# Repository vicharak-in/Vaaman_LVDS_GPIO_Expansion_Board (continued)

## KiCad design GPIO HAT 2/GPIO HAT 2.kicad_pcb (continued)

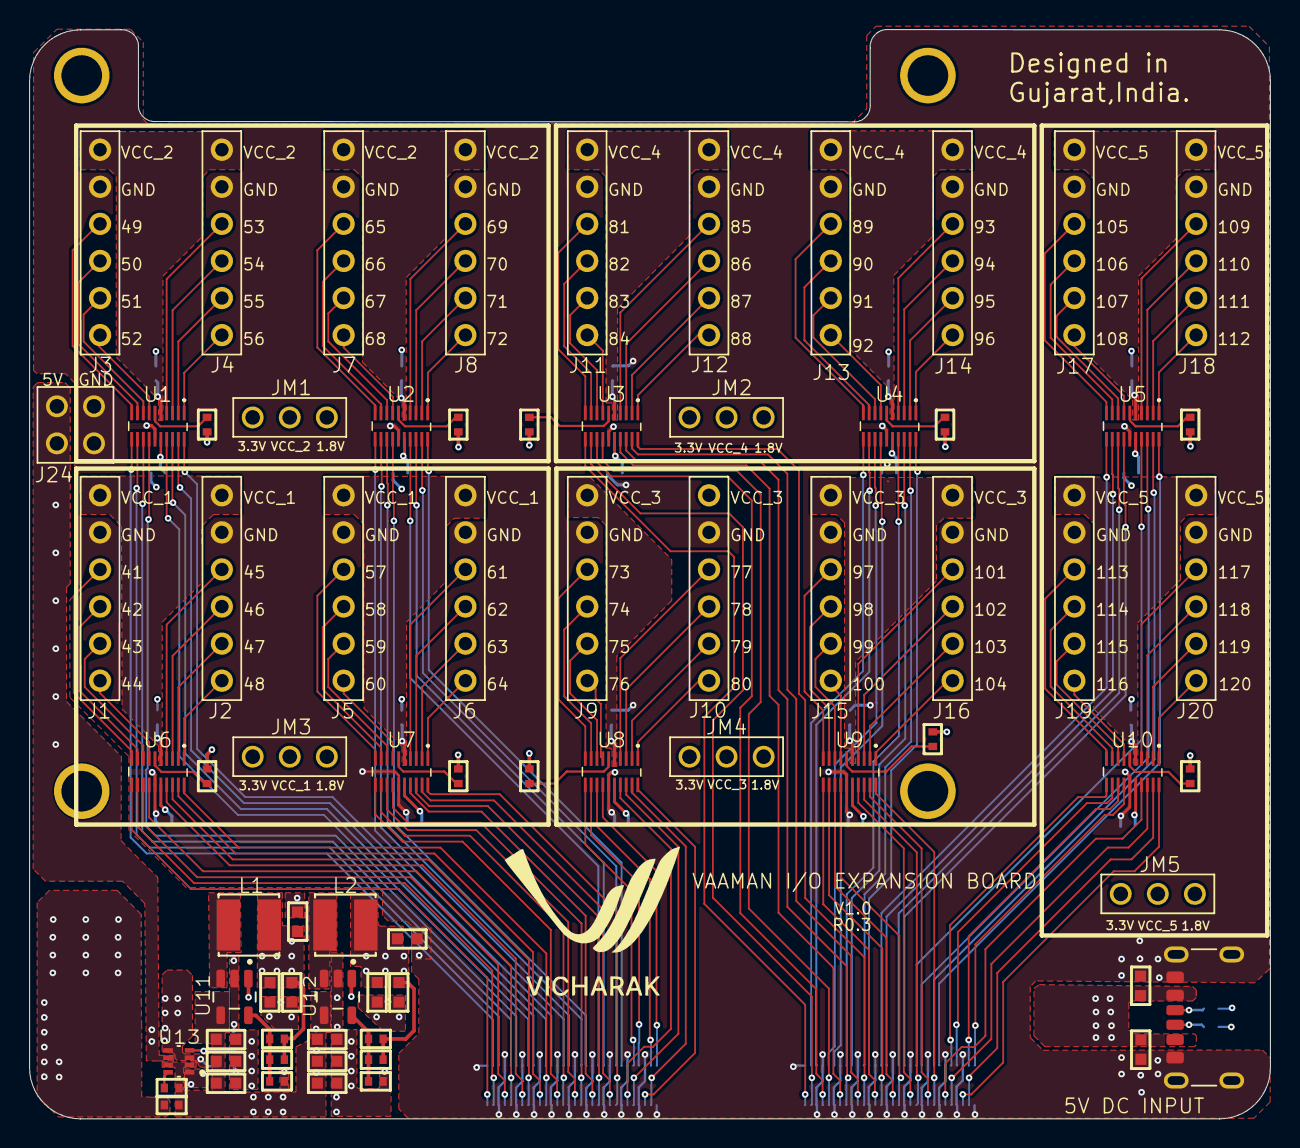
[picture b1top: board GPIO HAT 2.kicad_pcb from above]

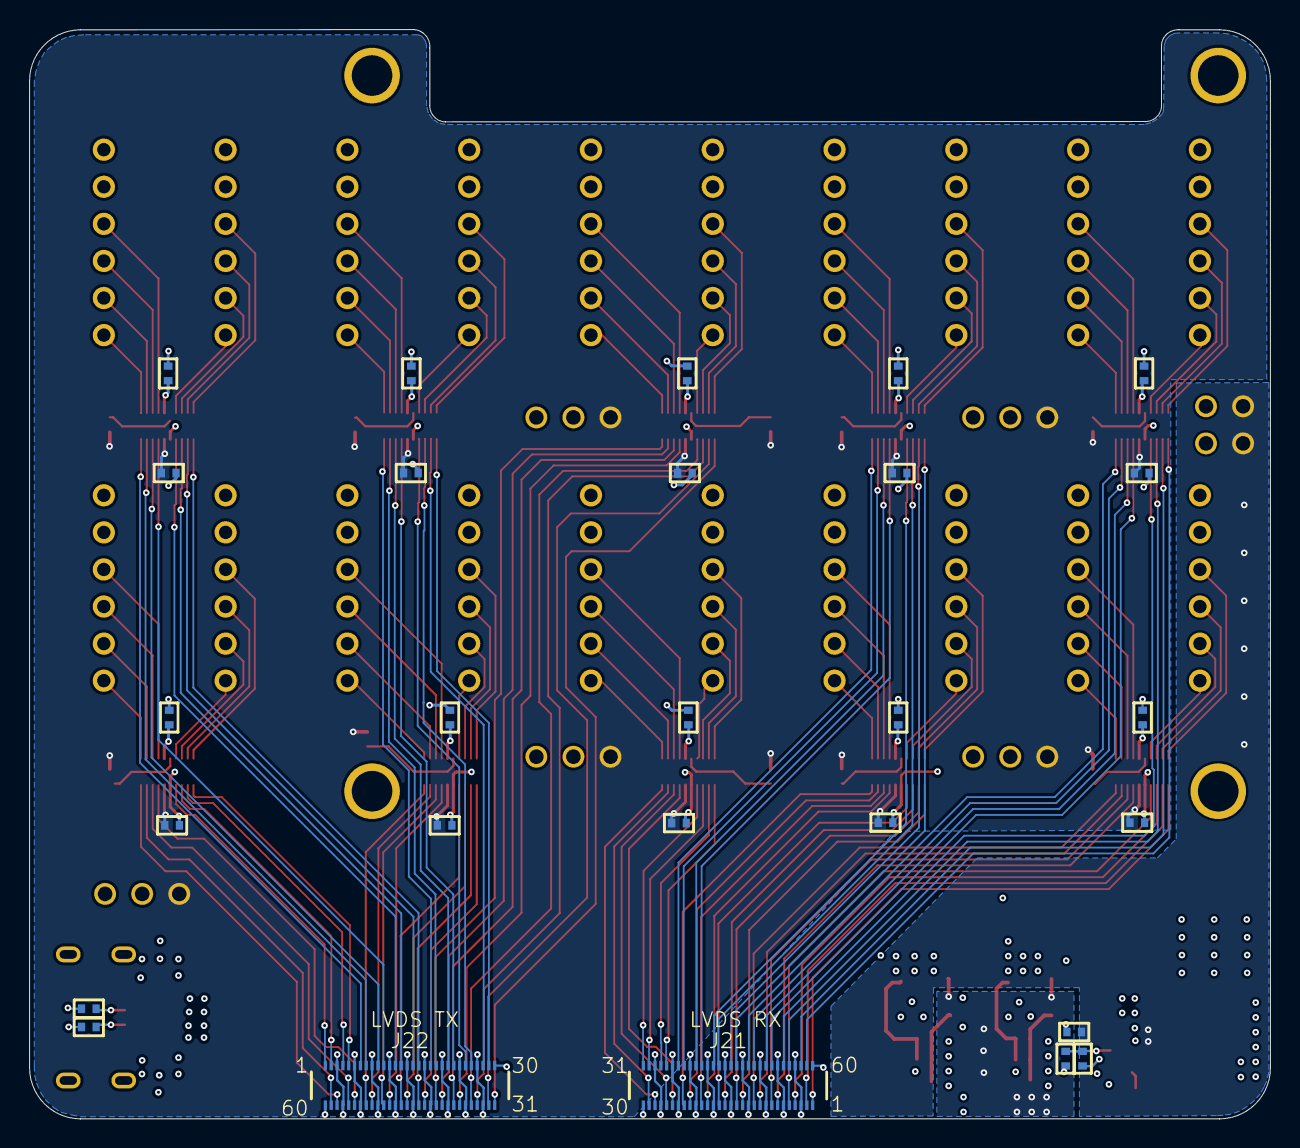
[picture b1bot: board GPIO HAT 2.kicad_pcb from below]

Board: 4 copper layers, 85.0 x 74.6 mm, 101 parts (27 on the bottom side), 189 nets.

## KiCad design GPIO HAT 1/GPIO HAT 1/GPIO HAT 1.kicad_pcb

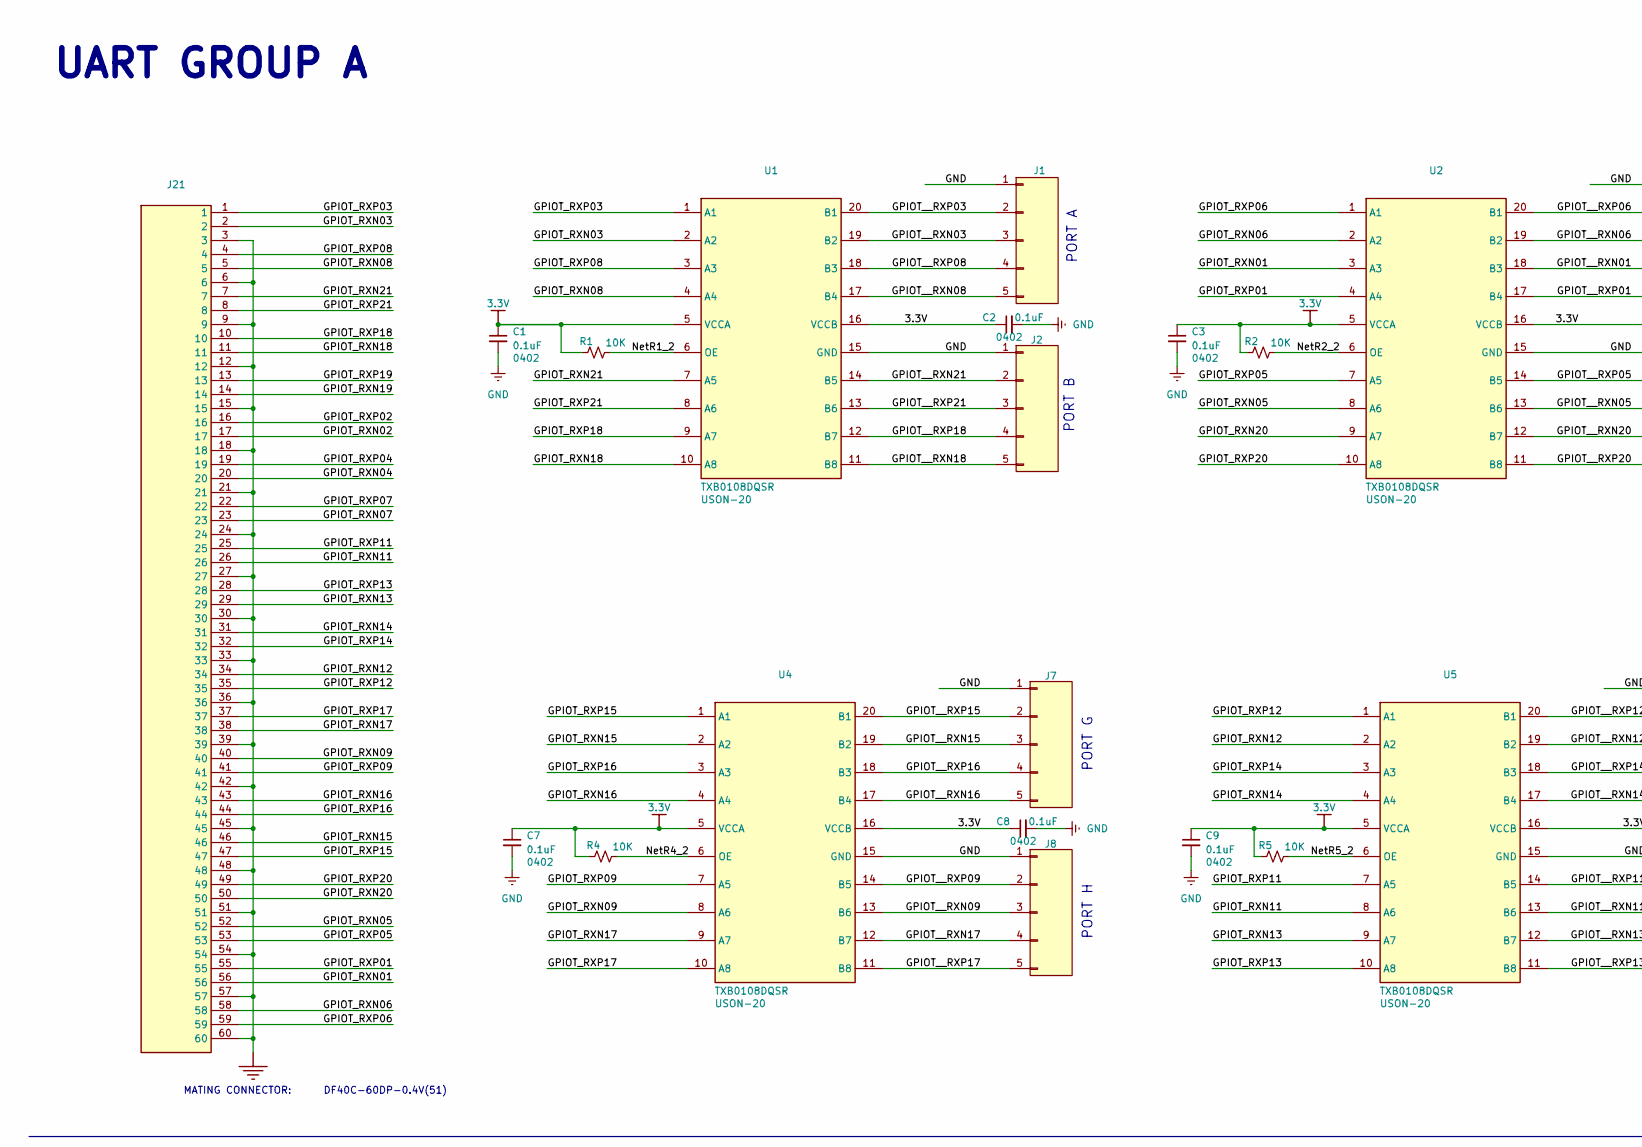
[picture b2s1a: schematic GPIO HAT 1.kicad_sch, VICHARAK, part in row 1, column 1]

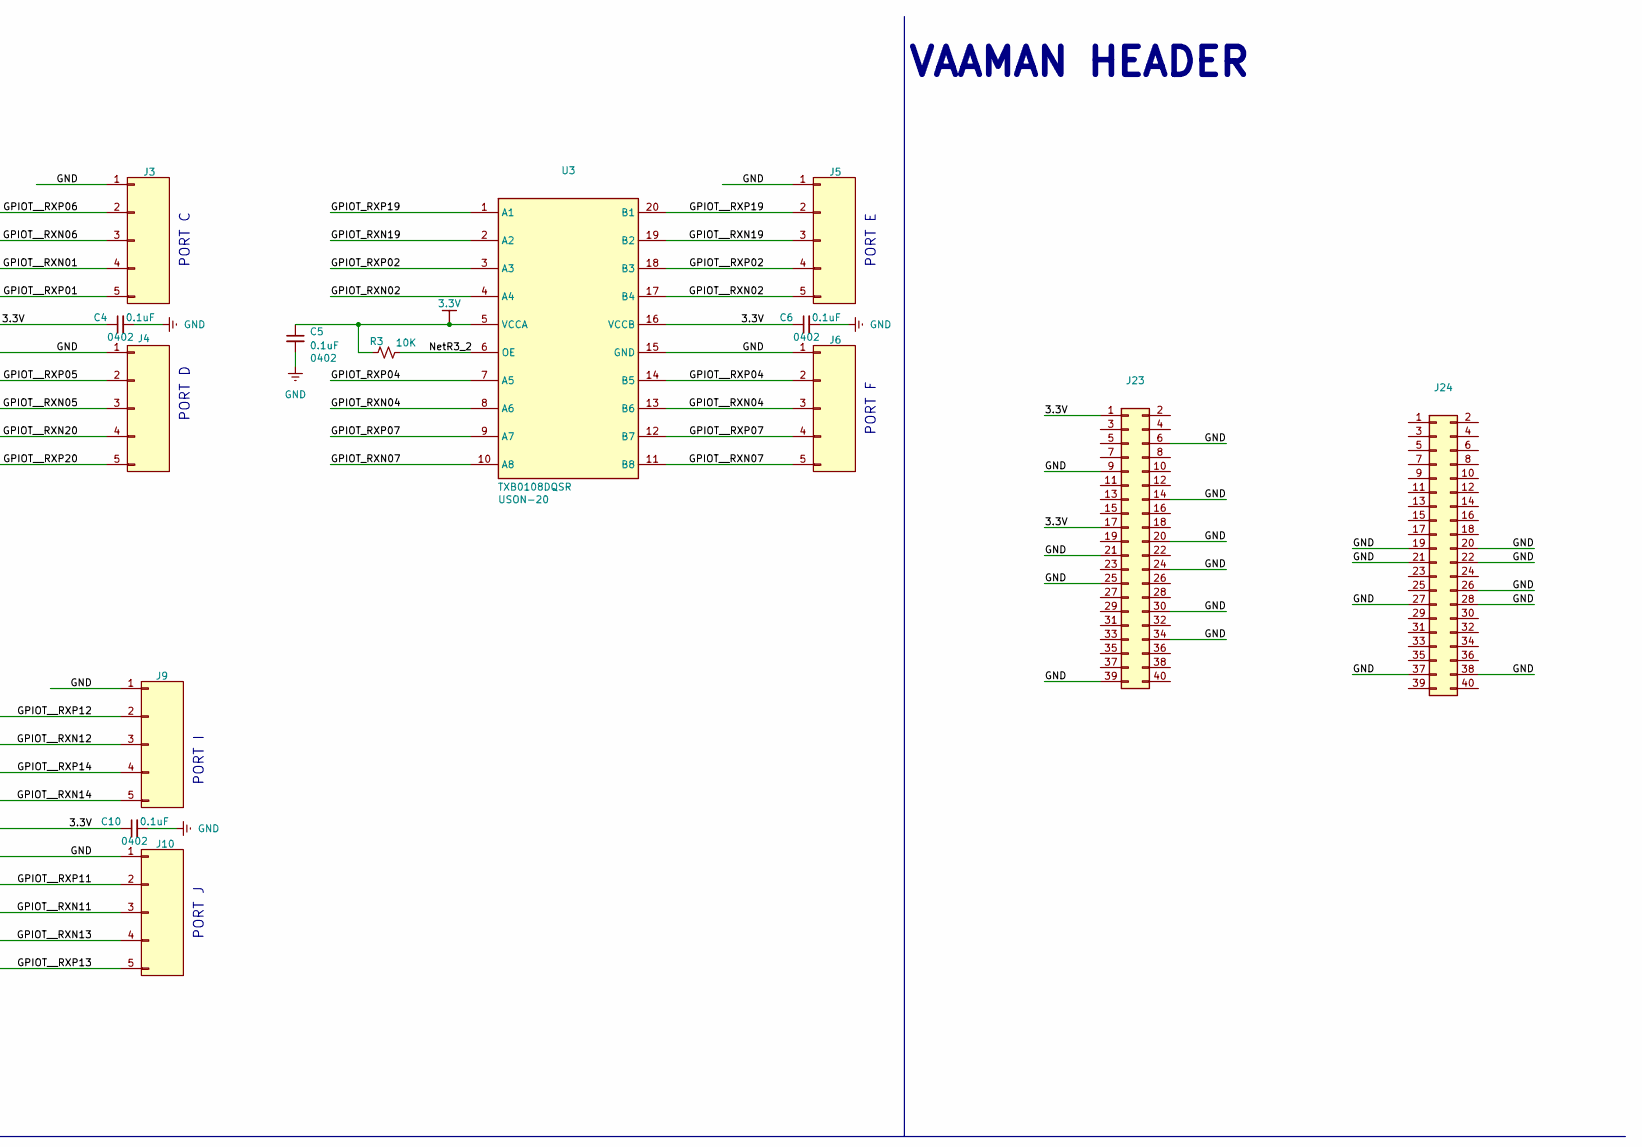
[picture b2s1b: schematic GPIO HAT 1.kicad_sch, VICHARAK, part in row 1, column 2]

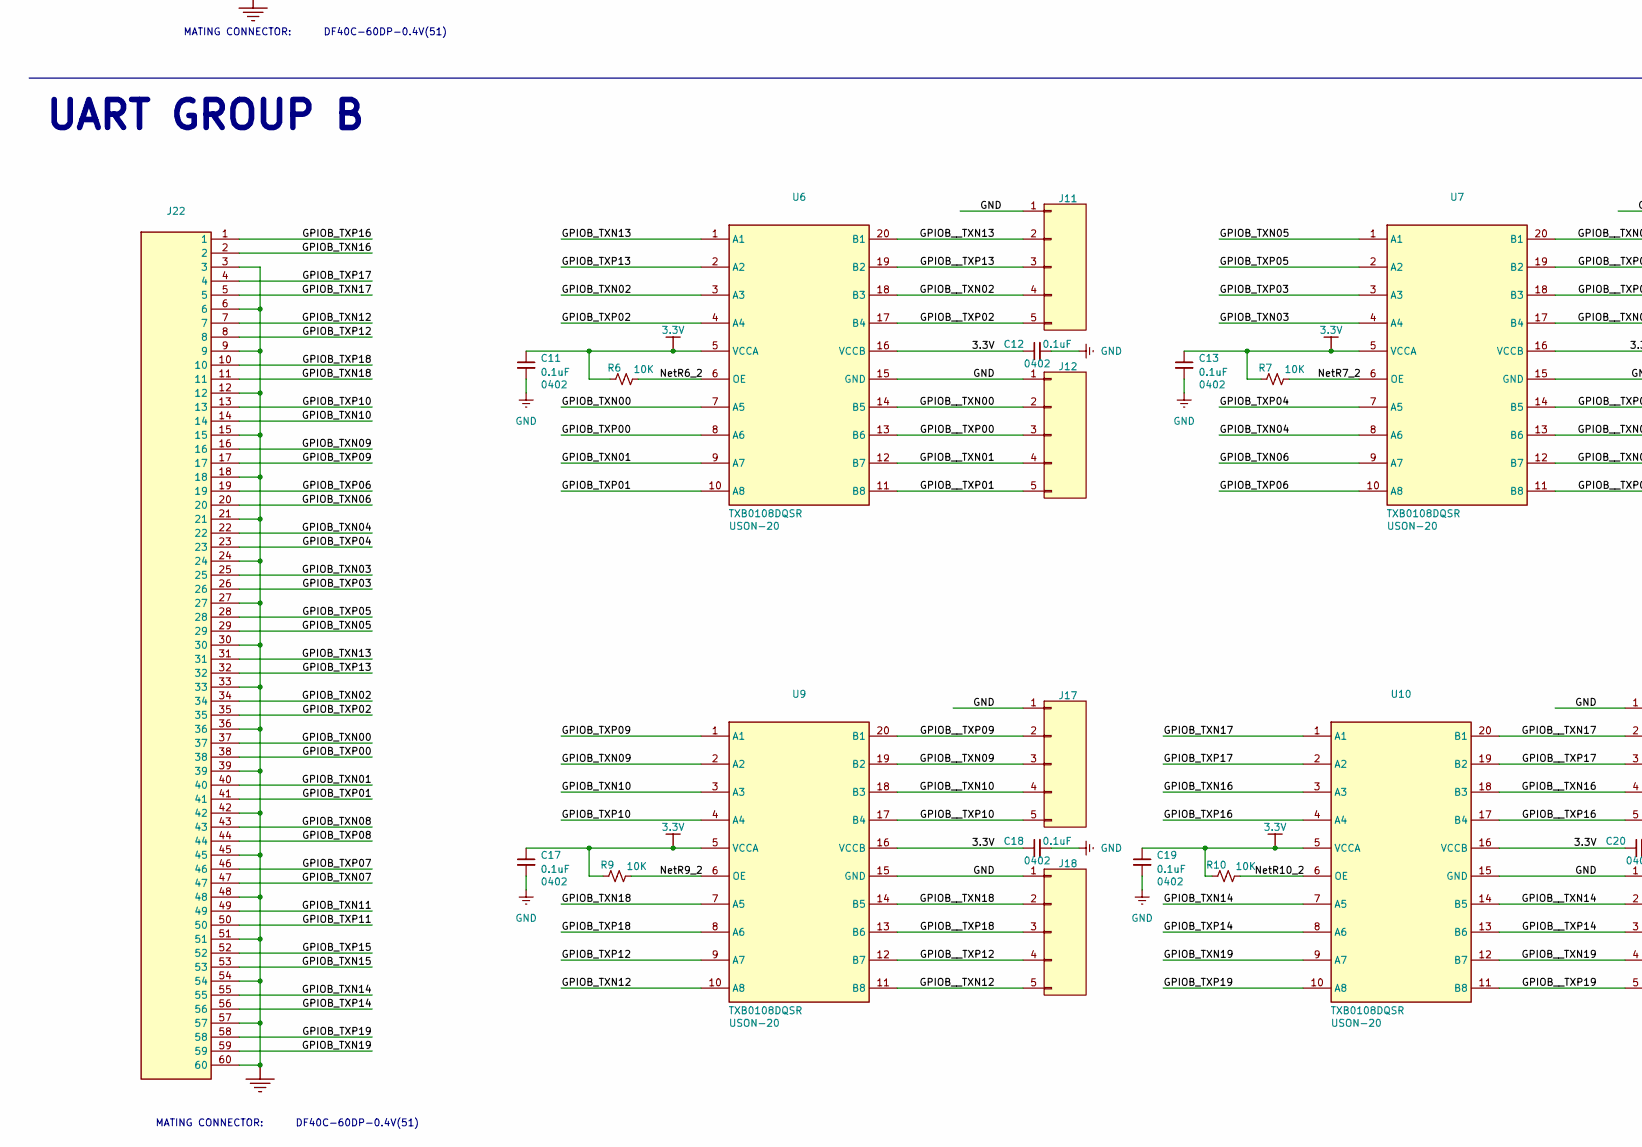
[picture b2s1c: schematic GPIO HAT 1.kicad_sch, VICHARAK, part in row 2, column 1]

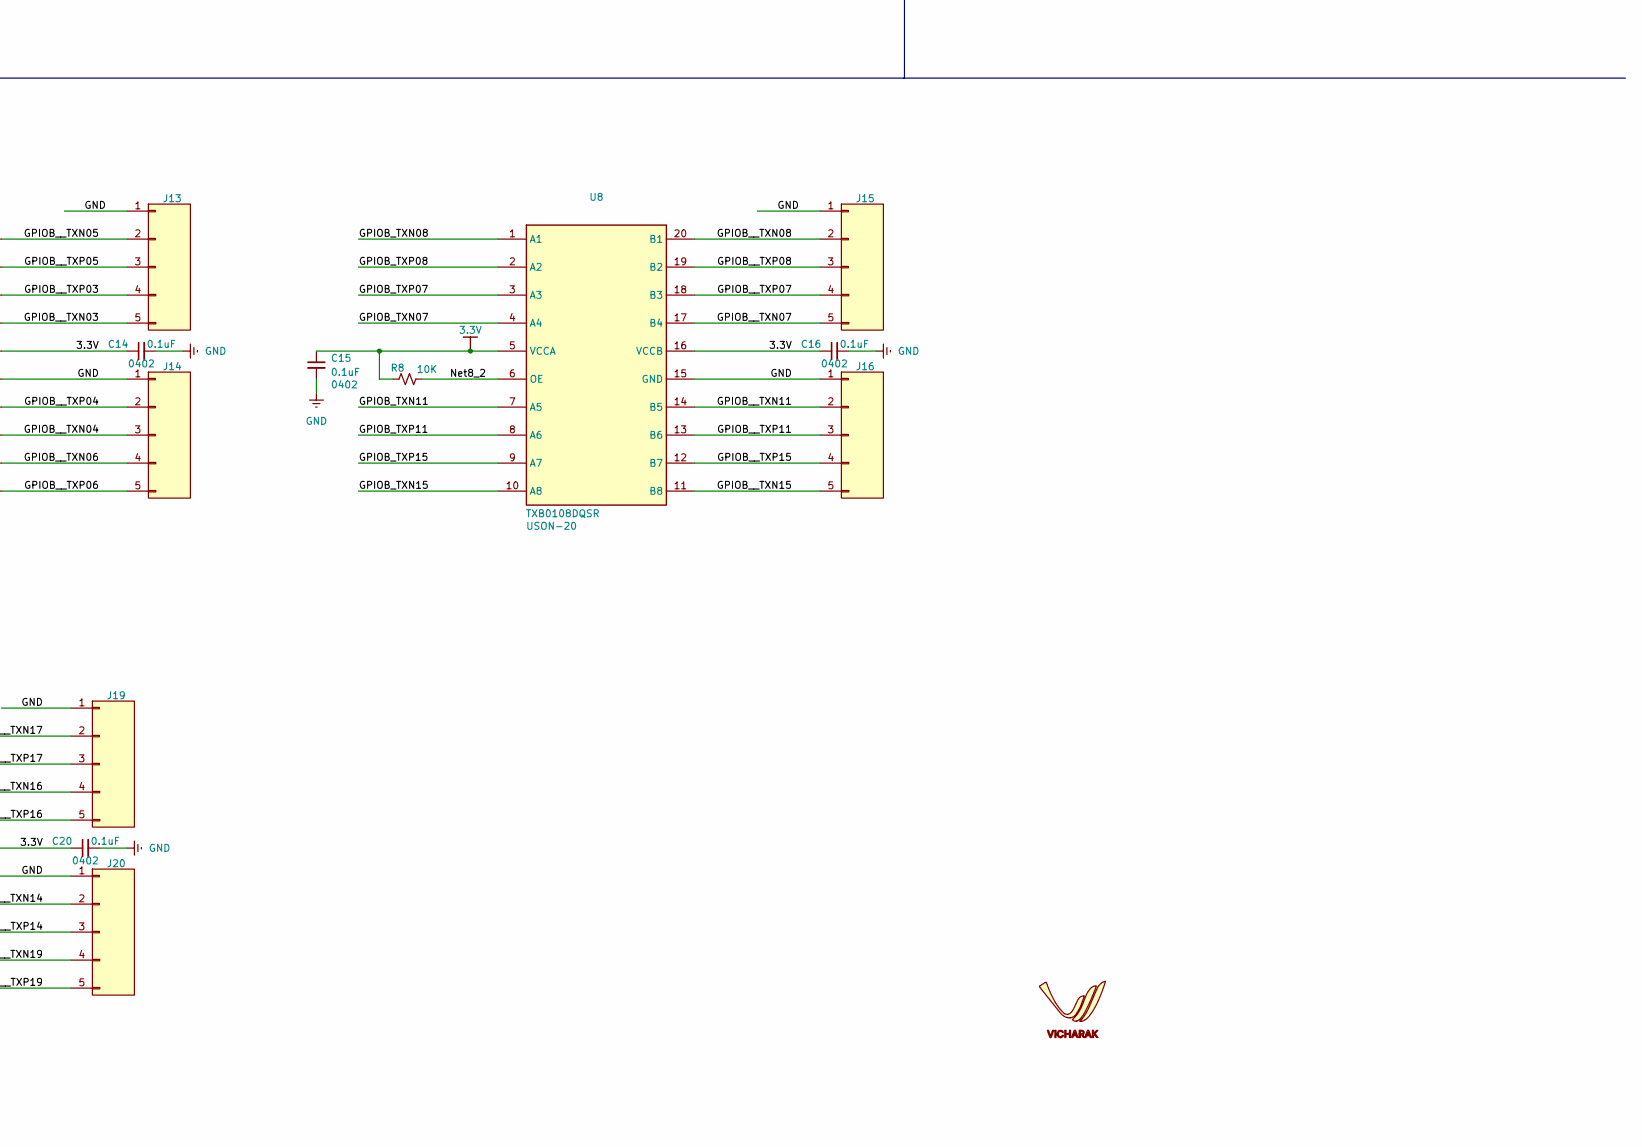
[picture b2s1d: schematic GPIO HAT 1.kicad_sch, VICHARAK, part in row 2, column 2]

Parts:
C1, C2, C3, C4, C5, C6, C7, C8, C9, C10, C11, C12, C13, C14, C15, C16, C17, C18, C19, C20: 0.1uF; CAP0402
J1, J2, J3, J4, J5, J6, J7, J8, J9, J10, J11, J12, J13, J14, J15, J16, J17, J18, J19, J20: Conn_01x05; 01x05 Header 2.54mm
J21, J22: LVDS2; Mouser Part Number 798-DF40C60DS0.4V51
J23, J24: 2.54-2*20PPC104; 2x20 header; MANUFACTURER PART NUMBER 2.54-2*20PPC104
R1, R2, R3, R4, R5, R6, R7, R8, R9, R10: 10K; RES0402_10K
U1, U2, U3, U4, U5, U6, U7, U8, U9, U10: TXB0108DQSR; Mouser Part Number 595-TXB0108DQSR

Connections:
3.3V: C1.1, C2.1, C3.1, C4.1, C5.1, C6.1, C7.1, C8.1, C9.1, C10.1, C11.1, C12.1, C13.1, C14.1, C15.1, C16.1, C17.1, C18.1, C19.1, C20.1, J23.1, J23.17, R1.1, R2.1, R3.1, R4.1, R5.1, R6.1, R7.1, R8.1, R9.1, R10.1, U1.5 (VCCA), U1.16 (VCCB), U2.5 (VCCA), U2.16 (VCCB), U3.5 (VCCA), U3.16 (VCCB), U4.5 (VCCA), U4.16 (VCCB), U5.5 (VCCA), U5.16 (VCCB), U6.5 (VCCA), U6.16 (VCCB), U7.5 (VCCA), U7.16 (VCCB), U8.5 (VCCA), U8.16 (VCCB), U9.5 (VCCA), U9.16 (VCCB), U10.5 (VCCA), U10.16 (VCCB)
/GPIOB_TXN00: J22.37, U6.7 (A5)
/GPIOB_TXN01: J22.40, U6.9 (A7)
/GPIOB_TXN02: J22.34, U6.3 (A3)
/GPIOB_TXN03: J22.25, U7.4 (A4)
/GPIOB_TXN04: J22.22, U7.8 (A6)
/GPIOB_TXN05: J22.29, U7.1 (A1)
/GPIOB_TXN06: J22.20, U7.9 (A7)
/GPIOB_TXN07: J22.47, U8.4 (A4)
/GPIOB_TXN08: J22.43, U8.1 (A1)
/GPIOB_TXN09: J22.16, U9.2 (A2)
/GPIOB_TXN10: J22.14, U9.3 (A3)
/GPIOB_TXN11: J22.49, U8.7 (A5)
/GPIOB_TXN12: J22.7, U9.10 (A8)
/GPIOB_TXN13: J22.31, U6.1 (A1)
/GPIOB_TXN14: J22.55, U10.7 (A5)
/GPIOB_TXN15: J22.53, U8.10 (A8)
/GPIOB_TXN16: J22.2, U10.3 (A3)
/GPIOB_TXN17: J22.5, U10.1 (A1)
/GPIOB_TXN18: J22.11, U9.7 (A5)
/GPIOB_TXN19: J22.59, U10.9 (A7)
/GPIOB_TXP00: J22.38, U6.8 (A6)
/GPIOB_TXP01: J22.41, U6.10 (A8)
/GPIOB_TXP02: J22.35, U6.4 (A4)
/GPIOB_TXP03: J22.26, U7.3 (A3)
/GPIOB_TXP04: J22.23, U7.7 (A5)
/GPIOB_TXP05: J22.28, U7.2 (A2)
/GPIOB_TXP06: J22.19, U7.10 (A8)
/GPIOB_TXP07: J22.46, U8.3 (A3)
/GPIOB_TXP08: J22.44, U8.2 (A2)
/GPIOB_TXP09: J22.17, U9.1 (A1)
/GPIOB_TXP10: J22.13, U9.4 (A4)
/GPIOB_TXP11: J22.50, U8.8 (A6)
/GPIOB_TXP12: J22.8, U9.9 (A7)
/GPIOB_TXP13: J22.32, U6.2 (A2)
/GPIOB_TXP14: J22.56, U10.8 (A6)
/GPIOB_TXP15: J22.52, U8.9 (A7)
/GPIOB_TXP16: J22.1, U10.4 (A4)
/GPIOB_TXP17: J22.4, U10.2 (A2)
/GPIOB_TXP18: J22.10, U9.8 (A6)
/GPIOB_TXP19: J22.58, U10.10 (A8)
/GPIOB__TXN00: J12.2, U6.14 (B5)
/GPIOB__TXN01: J12.4, U6.12 (B7)
/GPIOB__TXN02: J11.4, U6.18 (B3)
/GPIOB__TXN03: J13.5, U7.17 (B4)
/GPIOB__TXN04: J14.3, U7.13 (B6)
/GPIOB__TXN05: J13.2, U7.20 (B1)
/GPIOB__TXN06: J14.4, U7.12 (B7)
/GPIOB__TXN07: J15.5, U8.17 (B4)
/GPIOB__TXN08: J15.2, U8.20 (B1)
/GPIOB__TXN09: J17.3, U9.19 (B2)
/GPIOB__TXN10: J17.4, U9.18 (B3)
/GPIOB__TXN11: J16.2, U8.14 (B5)
/GPIOB__TXN12: J18.5, U9.11 (B8)
/GPIOB__TXN13: J11.2, U6.20 (B1)
/GPIOB__TXN14: J20.2, U10.14 (B5)
/GPIOB__TXN15: J16.5, U8.11 (B8)
/GPIOB__TXN16: J19.4, U10.18 (B3)
/GPIOB__TXN17: J19.2, U10.20 (B1)
/GPIOB__TXN18: J18.2, U9.14 (B5)
/GPIOB__TXN19: J20.4, U10.12 (B7)
/GPIOB__TXP00: J12.3, U6.13 (B6)
/GPIOB__TXP01: J12.5, U6.11 (B8)
/GPIOB__TXP02: J11.5, U6.17 (B4)
/GPIOB__TXP03: J13.4, U7.18 (B3)
/GPIOB__TXP04: J14.2, U7.14 (B5)
/GPIOB__TXP05: J13.3, U7.19 (B2)
/GPIOB__TXP06: J14.5, U7.11 (B8)
/GPIOB__TXP07: J15.4, U8.18 (B3)
/GPIOB__TXP08: J15.3, U8.19 (B2)
/GPIOB__TXP09: J17.2, U9.20 (B1)
/GPIOB__TXP10: J17.5, U9.17 (B4)
/GPIOB__TXP11: J16.3, U8.13 (B6)
/GPIOB__TXP12: J18.4, U9.12 (B7)
/GPIOB__TXP13: J11.3, U6.19 (B2)
/GPIOB__TXP14: J20.3, U10.13 (B6)
/GPIOB__TXP15: J16.4, U8.12 (B7)
/GPIOB__TXP16: J19.5, U10.17 (B4)
/GPIOB__TXP17: J19.3, U10.19 (B2)
/GPIOB__TXP18: J18.3, U9.13 (B6)
/GPIOB__TXP19: J20.5, U10.11 (B8)
/GPIOT_RXN01: J21.56, U2.3 (A3)
/GPIOT_RXN02: J21.17, U3.4 (A4)
/GPIOT_RXN03: J21.2, U1.2 (A2)
/GPIOT_RXN04: J21.20, U3.8 (A6)
/GPIOT_RXN05: J21.52, U2.8 (A6)
/GPIOT_RXN06: J21.58, U2.2 (A2)
/GPIOT_RXN07: J21.23, U3.10 (A8)
/GPIOT_RXN08: J21.5, U1.4 (A4)
/GPIOT_RXN09: J21.40, U4.8 (A6)
/GPIOT_RXN11: J21.26, U5.8 (A6)
/GPIOT_RXN12: J21.34, U5.2 (A2)
/GPIOT_RXN13: J21.29, U5.9 (A7)
/GPIOT_RXN14: J21.31, U5.4 (A4)
/GPIOT_RXN15: J21.46, U4.2 (A2)
/GPIOT_RXN16: J21.43, U4.4 (A4)
/GPIOT_RXN17: J21.38, U4.9 (A7)
/GPIOT_RXN18: J21.11, U1.10 (A8)
/GPIOT_RXN19: J21.14, U3.2 (A2)
/GPIOT_RXN20: J21.50, U2.9 (A7)
/GPIOT_RXN21: J21.7, U1.7 (A5)
/GPIOT_RXP01: J21.55, U2.4 (A4)
/GPIOT_RXP02: J21.16, U3.3 (A3)
/GPIOT_RXP03: J21.1, U1.1 (A1)
/GPIOT_RXP04: J21.19, U3.7 (A5)
/GPIOT_RXP05: J21.53, U2.7 (A5)
/GPIOT_RXP06: J21.59, U2.1 (A1)
/GPIOT_RXP07: J21.22, U3.9 (A7)
/GPIOT_RXP08: J21.4, U1.3 (A3)
/GPIOT_RXP09: J21.41, U4.7 (A5)
/GPIOT_RXP11: J21.25, U5.7 (A5)
/GPIOT_RXP12: J21.35, U5.1 (A1)
/GPIOT_RXP13: J21.28, U5.10 (A8)
/GPIOT_RXP14: J21.32, U5.3 (A3)
/GPIOT_RXP15: J21.47, U4.1 (A1)
/GPIOT_RXP16: J21.44, U4.3 (A3)
/GPIOT_RXP17: J21.37, U4.10 (A8)
/GPIOT_RXP18: J21.10, U1.9 (A7)
/GPIOT_RXP19: J21.13, U3.1 (A1)
/GPIOT_RXP20: J21.49, U2.10 (A8)
/GPIOT_RXP21: J21.8, U1.8 (A6)
/GPIOT__RXN01: J3.4, U2.18 (B3)
/GPIOT__RXN02: J5.5, U3.17 (B4)
/GPIOT__RXN03: J1.3, U1.19 (B2)
/GPIOT__RXN04: J6.3, U3.13 (B6)
/GPIOT__RXN05: J4.3, U2.13 (B6)
/GPIOT__RXN06: J3.3, U2.19 (B2)
/GPIOT__RXN07: J6.5, U3.11 (B8)
/GPIOT__RXN08: J1.5, U1.17 (B4)
/GPIOT__RXN09: J8.3, U4.13 (B6)
/GPIOT__RXN11: J10.3, U5.13 (B6)
/GPIOT__RXN12: J9.3, U5.19 (B2)
/GPIOT__RXN13: J10.4, U5.12 (B7)
/GPIOT__RXN14: J9.5, U5.17 (B4)
/GPIOT__RXN15: J7.3, U4.19 (B2)
/GPIOT__RXN16: J7.5, U4.17 (B4)
/GPIOT__RXN17: J8.4, U4.12 (B7)
/GPIOT__RXN18: J2.5, U1.11 (B8)
/GPIOT__RXN19: J5.3, U3.19 (B2)
/GPIOT__RXN20: J4.4, U2.12 (B7)
/GPIOT__RXN21: J2.2, U1.14 (B5)
/GPIOT__RXP01: J3.5, U2.17 (B4)
/GPIOT__RXP02: J5.4, U3.18 (B3)
/GPIOT__RXP03: J1.2, U1.20 (B1)
/GPIOT__RXP04: J6.2, U3.14 (B5)
/GPIOT__RXP05: J4.2, U2.14 (B5)
/GPIOT__RXP06: J3.2, U2.20 (B1)
/GPIOT__RXP07: J6.4, U3.12 (B7)
/GPIOT__RXP08: J1.4, U1.18 (B3)
/GPIOT__RXP09: J8.2, U4.14 (B5)
/GPIOT__RXP11: J10.2, U5.14 (B5)
/GPIOT__RXP12: J9.2, U5.20 (B1)
/GPIOT__RXP13: J10.5, U5.11 (B8)
/GPIOT__RXP14: J9.4, U5.18 (B3)
/GPIOT__RXP15: J7.2, U4.20 (B1)
/GPIOT__RXP16: J7.4, U4.18 (B3)
/GPIOT__RXP17: J8.5, U4.11 (B8)
/GPIOT__RXP18: J2.4, U1.12 (B7)
/GPIOT__RXP19: J5.2, U3.20 (B1)
/GPIOT__RXP20: J4.5, U2.11 (B8)
/GPIOT__RXP21: J2.3, U1.13 (B6)
/Net8_2: R8.2, U8.6 (OE)
/NetR1_2: R1.2, U1.6 (OE)
/NetR2_2: R2.2, U2.6 (OE)
/NetR3_2: R3.2, U3.6 (OE)
/NetR4_2: R4.2, U4.6 (OE)
/NetR5_2: R5.2, U5.6 (OE)
/NetR6_2: R6.2, U6.6 (OE)
/NetR7_2: R7.2, U7.6 (OE)
/NetR9_2: R9.2, U9.6 (OE)
/NetR10_2: R10.2, U10.6 (OE)
GND: C1.2, C2.2, C3.2, C4.2, C5.2, C6.2, C7.2, C8.2, C9.2, C10.2, C11.2, C12.2, C13.2, C14.2, C15.2, C16.2, C17.2, C18.2, C19.2, C20.2, J1.1, J2.1, J3.1, J4.1, J5.1, J6.1, J7.1, J8.1, J9.1, J10.1, J11.1, J12.1, J13.1, J14.1, J15.1, J16.1, J17.1, J18.1, J19.1, J20.1, J21.3, J21.6, J21.9, J21.12, J21.15, J21.18, J21.21, J21.24, J21.27, J21.30, J21.33, J21.36, J21.39, J21.42, J21.45, J21.48, J21.51, J21.54, J21.57, J21.60, J22.3, J22.6, J22.9, J22.12, J22.15, J22.18, J22.21, J22.24, J22.27, J22.30, J22.33, J22.36, J22.39, J22.42, J22.45, J22.48, J22.51, J22.54, J22.57, J22.60, J23.6, J23.9, J23.14, J23.20, J23.21, J23.24, J23.25, J23.30, J23.34, J23.39, J24.19, J24.20, J24.21, J24.22, J24.26, J24.27, J24.28, J24.37, J24.38, U1.15 (GND), U2.15 (GND), U3.15 (GND), U4.15 (GND), U5.15 (GND), U6.15 (GND), U7.15 (GND), U8.15 (GND), U9.15 (GND), U10.15 (GND)

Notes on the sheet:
PORT C
MATING CONNECTOR:
PORT G
PORT I
DF40C-60DP-0.4V(51)
VAAMAN HEADER
UART GROUP B
PORT H
UART GROUP A
PORT D
PORT F
PORT B
PORT E
PORT J
PORT A

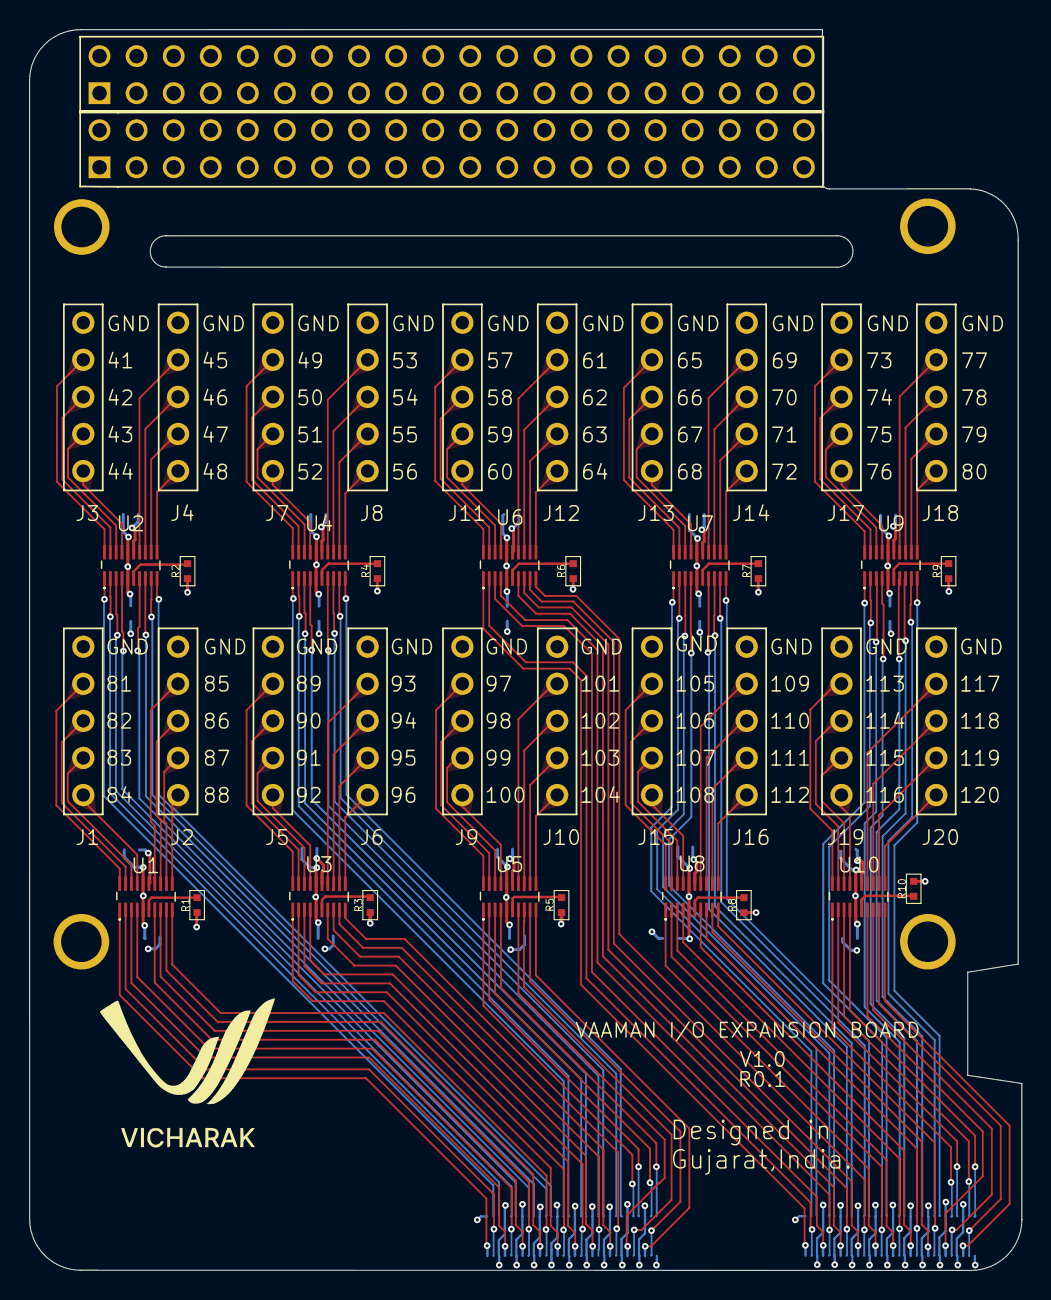
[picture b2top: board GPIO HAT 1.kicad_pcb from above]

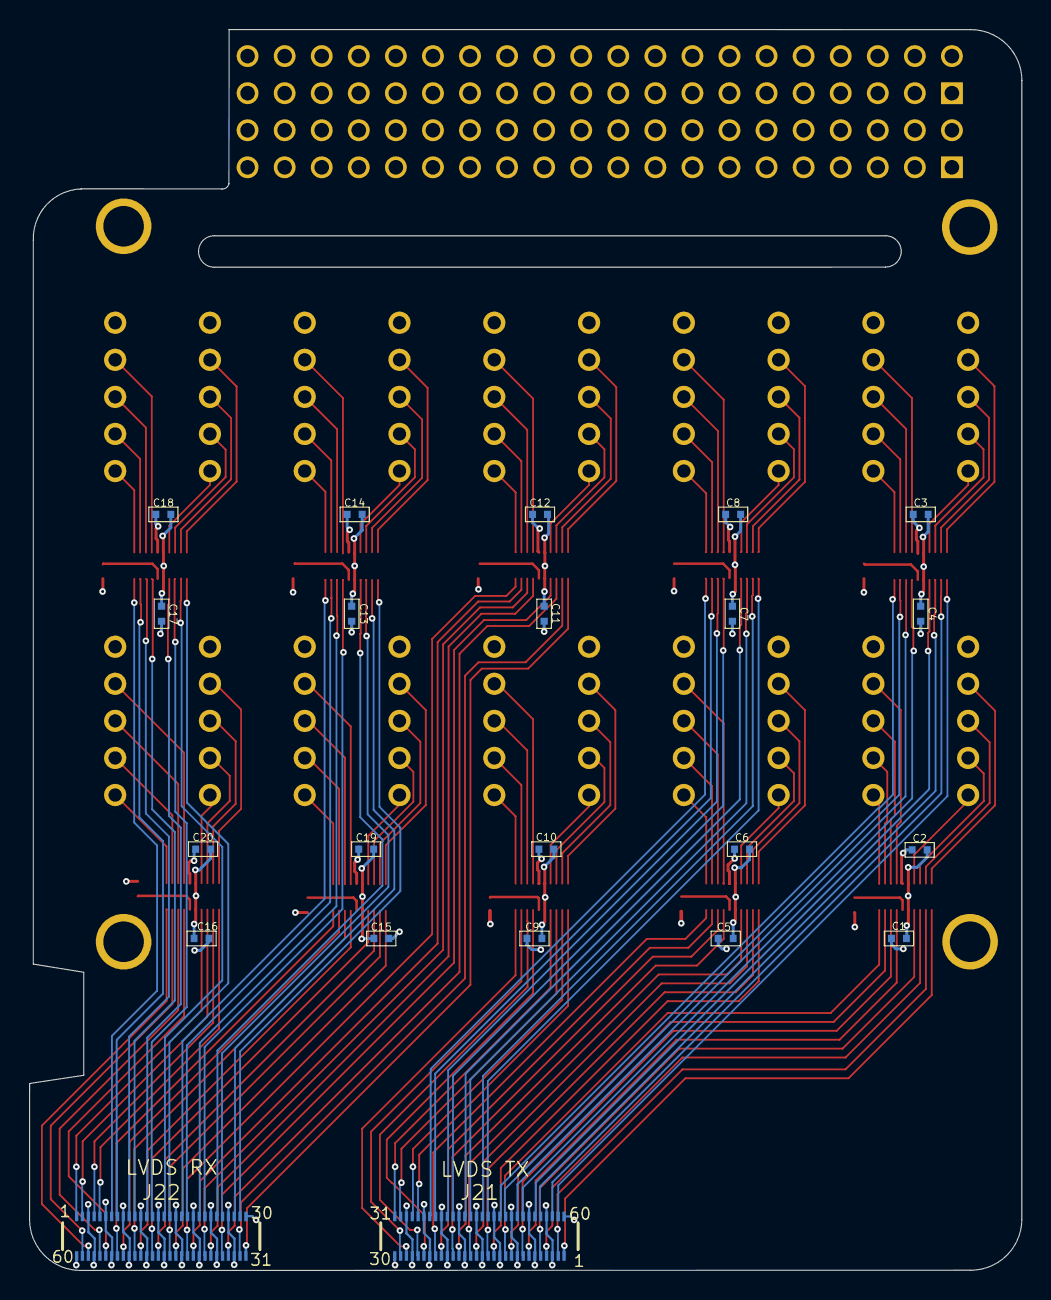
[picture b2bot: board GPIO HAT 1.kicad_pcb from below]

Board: 4 copper layers, 68.0 x 85.0 mm, 64 parts (22 on the bottom side), 172 nets.

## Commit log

2024-11-12 Version 1.0
2024-11-12 Version 1.1
2024-12-12 12V Jack removed and 5V USB added
2024-12-13 Ground plane added to top layer
2024-12-13 BOM and Gerber Generated
2024-12-13 Update
    Gerber Generated
2024-12-24 Copper in layer 2 added
2025-03-26 GPIO number change, CC1 & CC2 tied to GND
2025-03-26 Gerber Generated
2025-03-26 Folder Change
2025-04-10 Gerber genrated
    Overlay 64 pin to 88 pin
2025-05-16 Project file generated
    BOM, HTML , PDFs
2025-07-18 BOM and HTML Update
